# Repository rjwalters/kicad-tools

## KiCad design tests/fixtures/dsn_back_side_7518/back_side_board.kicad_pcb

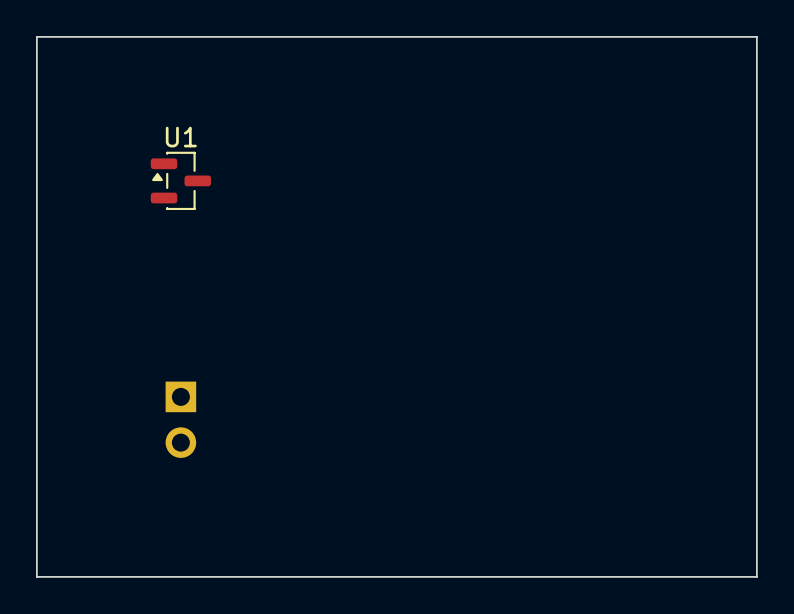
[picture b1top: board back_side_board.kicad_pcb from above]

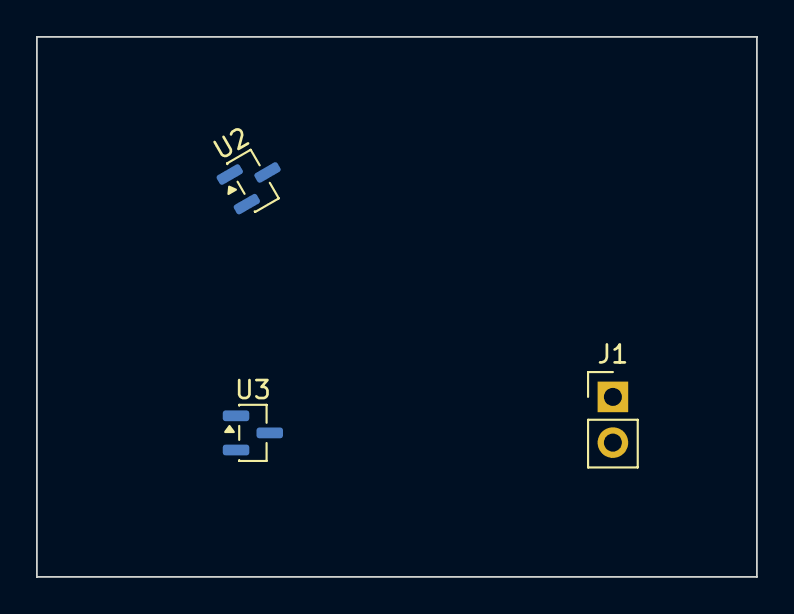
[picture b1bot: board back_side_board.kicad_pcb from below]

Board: 2 copper layers, 40.0 x 30.0 mm, 4 parts (3 on the bottom side), 4 nets, no tracks yet.

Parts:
J1: PinHeader_1x02_P2.54mm_Vertical
U1, U2, U3: SOT-23

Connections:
BB: U2.1, U3.1
FB: U1.1, U2.2
FT: J1.2, U1.2
TB: J1.1, U3.2

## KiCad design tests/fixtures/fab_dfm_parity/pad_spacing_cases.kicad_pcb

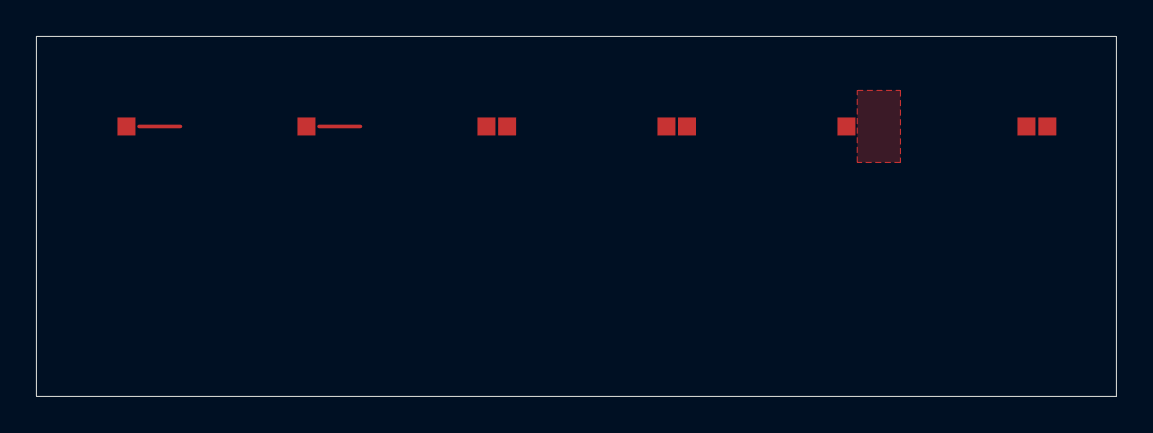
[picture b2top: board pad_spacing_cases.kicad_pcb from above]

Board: 2 copper layers, 60.0 x 20.0 mm, 9 parts (0 on the bottom side), 2 nets.

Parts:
P1: P1
P2: P2
P3: P3
P4: P4
P5: P5
P6: P6
P7: P7
P8: P8
P9: P9

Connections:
A: P1.1, P2.1, P3.1, P5.1, P7.1, P8.1
B: P4.1, P6.1, P9.1
